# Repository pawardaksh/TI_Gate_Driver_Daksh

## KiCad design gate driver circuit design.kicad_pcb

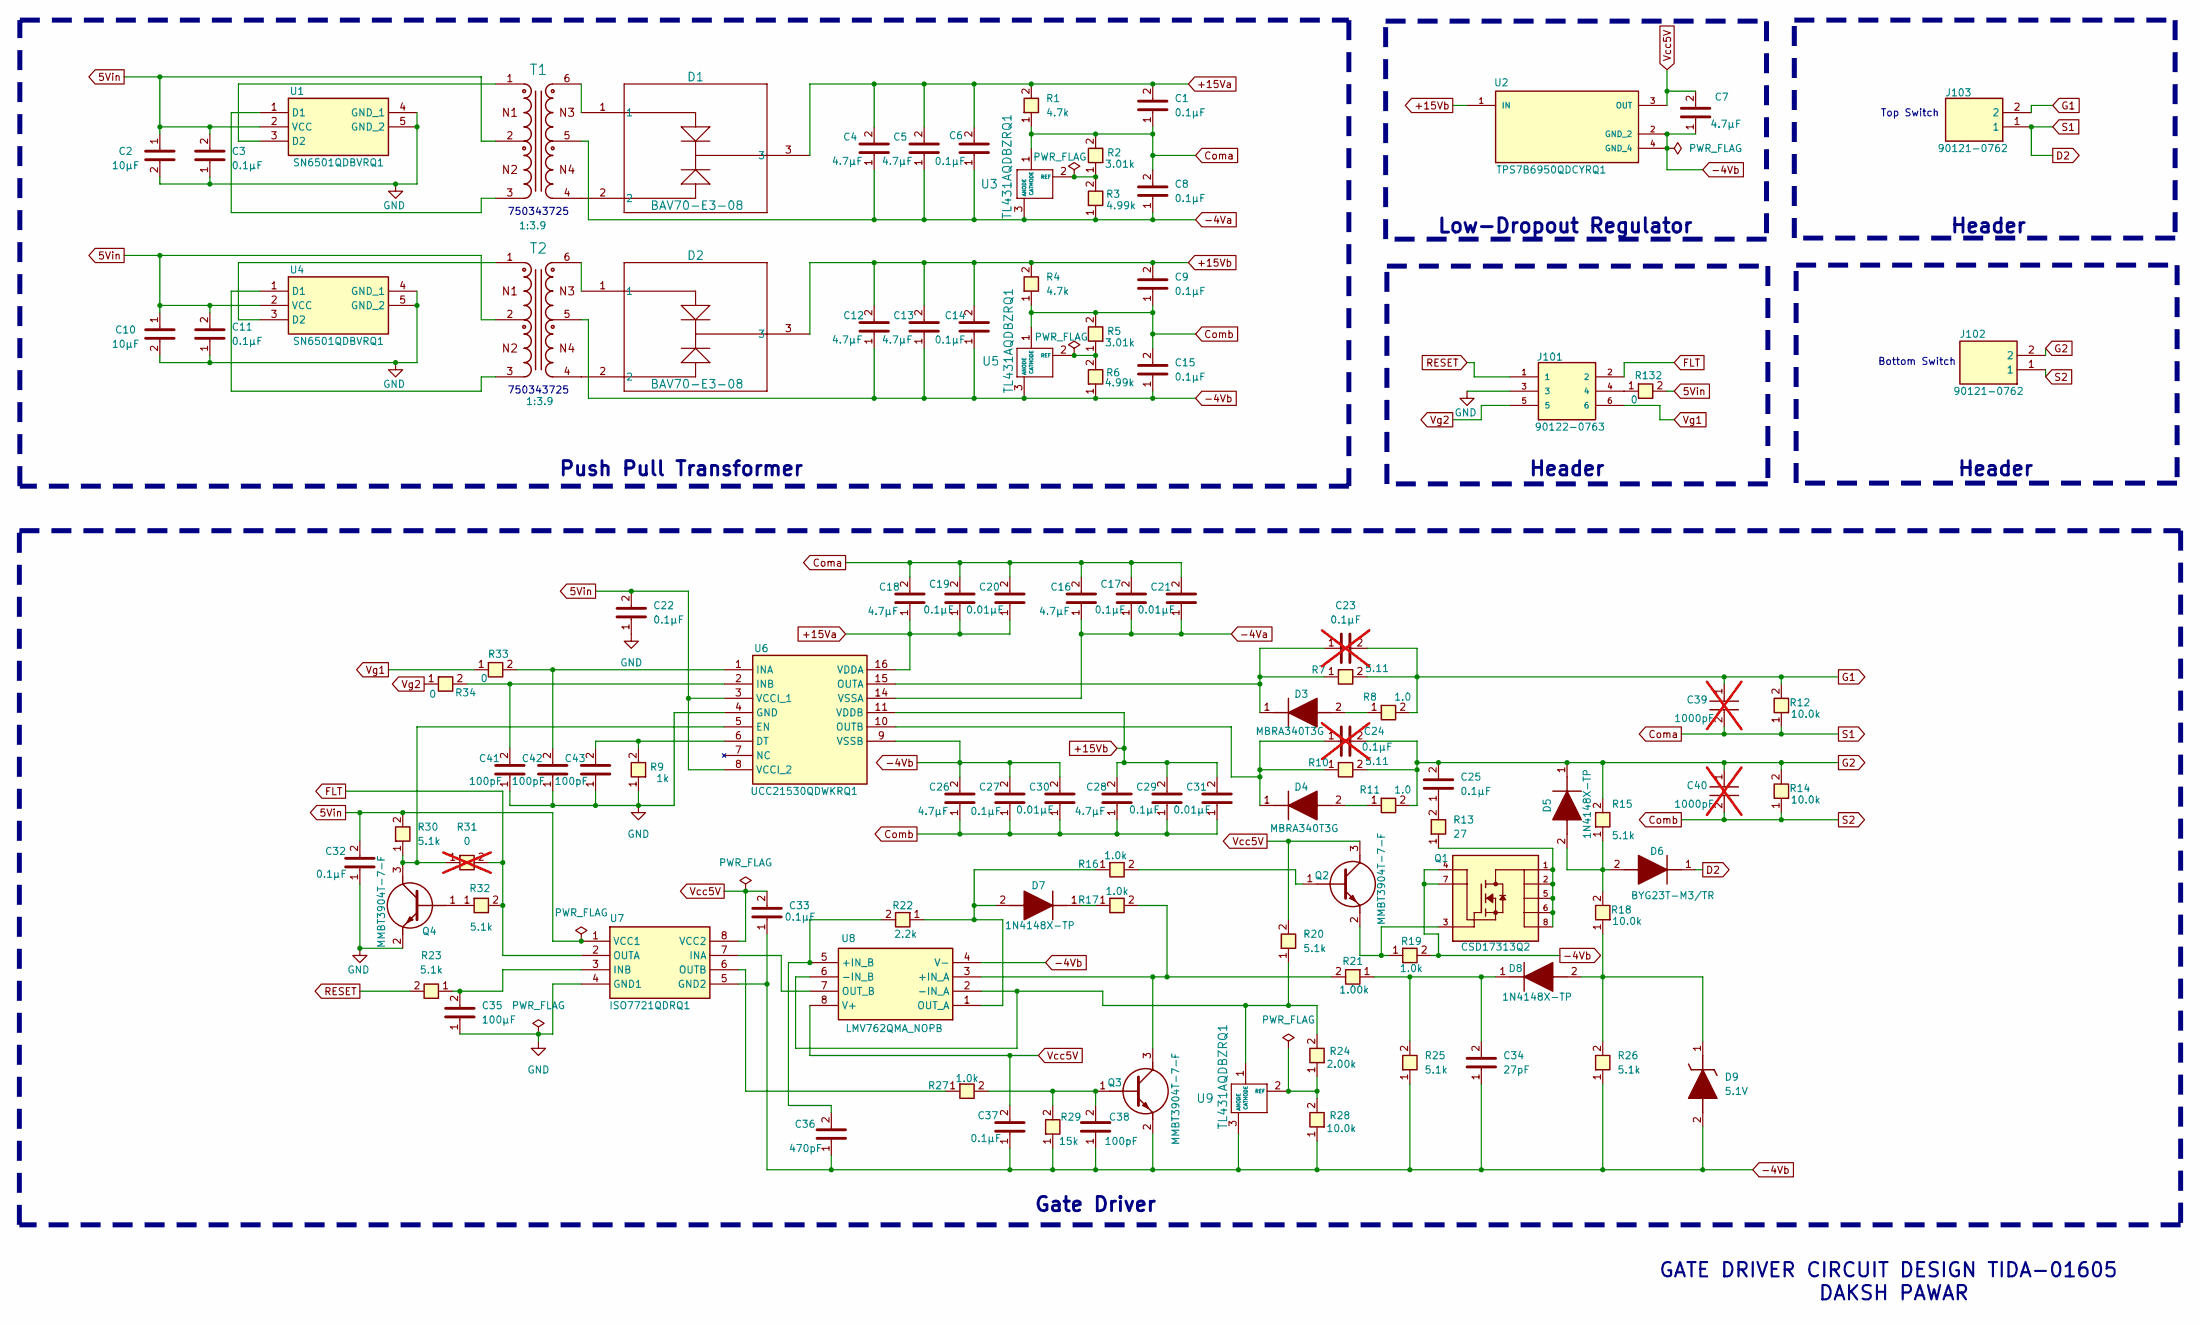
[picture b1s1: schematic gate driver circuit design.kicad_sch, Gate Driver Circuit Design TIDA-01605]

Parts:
C1, C3, C6, C8, C9, C11, C14, C15, C17, C19, C22, C25, C27, C29, C32, C33, C37: 0.1µF; CAPC2012X90N; Mouser Part Number 791-0805B104K250CT
C2, C10: 10µF; CAPC2012X135N; Mouser Part Number 963-LMK212ABJ106KGHT
C4, C5, C7, C12, C13, C16, C18, C26, C28: 4.7µF; GRT21BR61E226ME13L; Mouser Part Number 81-GRT21BR61H475KE3L
C20, C21, C30, C31: 0.01µF; CAPC2012X95N; Mouser Part Number 81-GRM215C1H103JA01D
C23, C24: 0.1µF; CAPC2012X95N; Mouser Part Number 603-AC805KRX7R8BB104; not fitted
C34: 27pF; CAPC2012X70N; Mouser Part Number 603-CC805JRNPO9BN270
C35: 100µF; CAPC2012X75N; Mouser Part Number 187-CL21C101JBANNNC
C36: 470pF; C0805; Mouser Part Number 80-C0805C471J5G
C38, C41, C42, C43: 100pF; C0805; Mouser Part Number 80-C0805C101J1GAUTO
C39, C40: 1000pF; C0805; Manufacturer_Part_Number C0805C102K5RACAUTO; not fitted
D1, D2: BAV70-E3-08; SOT_70-E3-08_VIS
D3, D4: MBRA340T3G; DIOM5226X220N; Manufacturer_Part_Number MBRA340T3G; Mouser Part Number 863-MBRA340T3G
D5, D7, D8: 1N4148X-TP; SODFL1608X70N; Manufacturer_Part_Number 1N4148X-TP; Mouser Part Number 833-1N4148X-TP
D6: BYG23T-M3/TR; DIOM5127X229N; Manufacturer_Part_Number BYG23T-M3/TR; Mouser Part Number 78-BYG23T-M3/TR
D9: 5.1V; SOD3716X135N; Mouser Part Number 78-BZT52C5V1-G3-08
J101: 90122-0763; MOLEX_90122-0763; PARTREV M3
J102, J103: 90121-0762; HDRRA2W64P0X254_1X2_508X250X360P; Mouser Part Number 538-90121-0762
Q1: CSD17313Q2; TRANS_CSD17313Q2; PARTREV E
Q2, Q3, Q4: MMBT3904T-7-F; SOT50P160X90-3N; Manufacturer_Part_Number MMBT3904T-7-F; Mouser Part Number 621-MMBT3904T-F
R1, R4: 4.7k; RESC2012X50N; Mouser Part Number 71-CRCW0805J-4.7K-E3
R2, R5: 3.01k; RESC2012X60N; Mouser Part Number 603-RT0805DRE073K01L
R3, R6: 4.99k; RESC2013X65N; Mouser Part Number 754-RR1220P-4991D-M
R7, R10: 5.11; RESC3216X60N; Mouser Part Number 71-CRCW12065R11FKEA
R8, R11: 1.0; RESC3116X65N; Mouser Part Number 652-CRM1206JW1R0ELF
R9: 1k; RESC2012X60N; Mouser Part Number 652-CR0805-F/1R00ELF
R12, R14: 10.0k; RESC2012X60N; Mouser Part Number 71-CRCW080510K0FKEBC
R13: 27; RESC3216X60N; Mouser Part Number 71-CRCW1206J-27-E3
R15, R20, R23, R25, R26, R30, R32: 5.1k; RESC2012X60N; Mouser Part Number 652-CR0805FX-5101ELF
R16, R17, R19, R27: 1.0k; RESC2012X60N; Mouser Part Number 603-RC0805JR-131KL
R18: 10.0k; RESC2012X60N; Mouser Part Number 667-ERA-6AEB103V
R21: 1.00k; RESC2012X60N; Mouser Part Number 791-RMC1/16K102FTP
R22: 2.2k; RESC2012X60N; Mouser Part Number 652-CR0805JW-222ELF
R24: 2.00k; RESC2012X60N; Mouser Part Number 708-RNCP0805FTD2K00
R28: 10.0k; RESC2012X60N; Mouser Part Number 708-RNCF0805DTE10K0
R29: 15k; RESC2012X50N; Mouser Part Number 71-CRCW0805J-15K-E3
R31: 0; ERJS06_U06__0805_; Mouser Part Number 667-ERJ-U060R00V; not fitted
R33: 0; RESC2012X60N; Mouser Part Number 667-ERJ-U060R00V
R34, R132: 0; ERJS06_U06__0805_; Mouser Part Number 667-ERJ-U060R00V
T1, T2: 750343725; TRANSFORMER_750343725_WRE-L; Input Voltage 5VDC; Output Voltage 1 19.5V; Manufacturer Part Number 750343725
U1, U4: SN6501QDBVRQ1; SOT95P280X145-5N; Mouser Part Number 595-SN6501QDBVRQ1
U2: TPS7B6950QDCYRQ1; VREG_TPS7B6950QDCYRQ1; PARTREV B
U3, U5, U9: TL431AQDBZRQ1; DBZ3
U6: UCC21530QDWKRQ1; Manufacturer_Part_Number UCC21530QDWKRQ1; Mouser Part Number 595-UCC21530QDWKRQ1
U7: ISO7721QDRQ1; SOIC127P600X175-8N; Manufacturer_Part_Number ISO7721QDRQ1; Mouser Part Number 595-ISO7721QDRQ1
U8: LMV762QMA_NOPB; SOIC127P600X175-8N; Manufacturer_Part_Number LMV762QMA/NOPB; Mouser Part Number 595-LMV762QMA/NOPB

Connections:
5Vin: C2.1, C3.2, C10.1, C11.2, C22.2, C32.2, R30.2, R132.2, T1.2, T2.2, U1.2 (VCC), U4.2 (VCC), U6.3 (VCCI_1), U6.8 (VCCI_2), U7.1 (VCC1)
+15Va: C1.2, C4.2, C5.2, C6.2, C18.1, C19.1, C20.1, D1.3, R1.2, U6.16 (VDDA)
+15Vb: C9.2, C12.2, C13.2, C14.2, C28.2, C29.2, C31.2, D2.3, R4.2, U2.1 (IN), U6.11 (VDDB)
-4Va: C4.1, C5.1, C6.1, C8.1, C16.1, C17.1, C21.1, R3.1 (R1), T1.5, U3.3 (ANODE), U6.14 (VSSA)
-4Vb: C7.1, C12.1, C13.1, C14.1, C15.1, C26.2, C27.2, C30.2, C33.1, C34.1, C36.1, C37.1, C38.1, D9.2 (A), Q1.4, Q1.7, Q3.2 (E), R6.1 (R1), R19.2, R25.1, R26.1, R28.1, R29.1, T2.5, U2.2 (GND_2), U2.4 (GND_4), U5.3 (ANODE), U6.9 (VSSB), U7.5 (GND2), U8.4 (V-), U9.3 (ANODE)
Coma: C1.1, C8.2, C16.2, C17.2, C18.2, C19.2, C20.2, C21.2, C39.2, D6.1 (K), J103.1, R1.1, R2.2, R12.1, U3.1 (CATHODE)
Comb: C9.1, C15.2, C26.1, C27.1, C28.1, C29.1, C30.1, C31.1, C40.2, J102.1, R4.1, R5.2, R14.1, U5.1 (CATHODE)
FLT: J101.2, R31.2, R32.2, U7.2 (OUTA)
G1: C23.2, C39.1, J103.2, R7.2, R8.2, R12.2
G2: C24.2, C25.2, C40.1, D5.1 (K), J102.2, R10.2, R11.2, R14.2, R15.2
GND: C2.2, C3.1, C10.2, C11.1, C22.1, C32.1, C35.1, C41.1, C42.1, C43.1, J101.3, Q4.2 (E), R9.1, U1.4 (GND_1), U1.5 (GND_2), U4.4 (GND_1), U4.5 (GND_2), U6.4 (GND), U7.4 (GND1)
unnamed: C25.1, R13.2
unnamed: D1.1, T1.6
unnamed: D1.2, T1.4
unnamed: D2.1, T2.6
unnamed: D2.2, T2.4
unnamed: D3.2 (A), R8.1
unnamed: C23.1, D3.1 (K), R7.1, U6.15 (OUTA)
unnamed: D4.2 (A), R11.1
unnamed: C24.1, D4.1 (K), R10.1, U6.10 (OUTB)
unnamed: D5.2 (A), D6.2 (A), R15.1, R18.2
unnamed: D7.2 (A), R16.1, R22.1, U8.1 (OUT_A)
unnamed: D7.1 (K), R17.1
unnamed: D8.2 (A), D9.1 (K), R18.1, R26.2
unnamed: C34.2, D8.1 (K), R21.1, R25.2
unnamed: J101.4, R132.1
unnamed: Q1.1, Q1.2, Q1.5, Q1.6, Q1.8, R13.1
unnamed: Q2.1 (B), R16.2
unnamed: Q1.3, Q2.2 (E), R19.1
unnamed: C38.2, Q3.1 (B), R27.2, R29.2
unnamed: Q3.3 (C), R17.2, R21.2, U8.3 (+IN_A)
unnamed: Q4.1 (B), R32.1
unnamed: Q4.3 (C), R30.1, R31.1, U6.5 (EN)
unnamed: R2.1, R3.2 (R2), U3.2 (REF)
unnamed: R5.1, R6.2 (R2), U5.2 (REF)
unnamed: T1.3, U1.1 (D1)
unnamed: T1.1, U1.3 (D2)
unnamed: T2.3, U4.1 (D1)
unnamed: T2.1, U4.3 (D2)
unnamed: C43.2, R9.2, U6.6 (DT)
unnamed: C42.2, R33.2, U6.1 (INA)
unnamed: C41.2, R34.2, U6.2 (INB)
unnamed: U7.7 (INA), U8.7 (OUT_B)
unnamed: C35.2, R23.1, U7.3 (INB)
unnamed: R27.1, U7.6 (OUTB)
unnamed: C36.2, R22.2, U8.5 (+IN_B)
unnamed: R20.1, R24.2, U8.2 (-IN_A), U8.6 (-IN_B), U9.1 (CATHODE)
unnamed: R24.1, R28.2, U9.2 (REF)
RESET: J101.1, R23.2
Vcc5V: C7.2, C33.2, C37.2, Q2.3 (C), R20.2, U2.3 (OUT), U7.8 (VCC2), U8.8 (V+)
Vg1: J101.6, R33.1
Vg2: J101.5, R34.1

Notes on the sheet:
GATE DRIVER CIRCUIT DESIGN TIDA-01605 DAKSH PAWAR
750343725
Bottom Switch
Header
Gate Driver
Top Switch
Push Pull Transformer
Low-Dropout Regulator

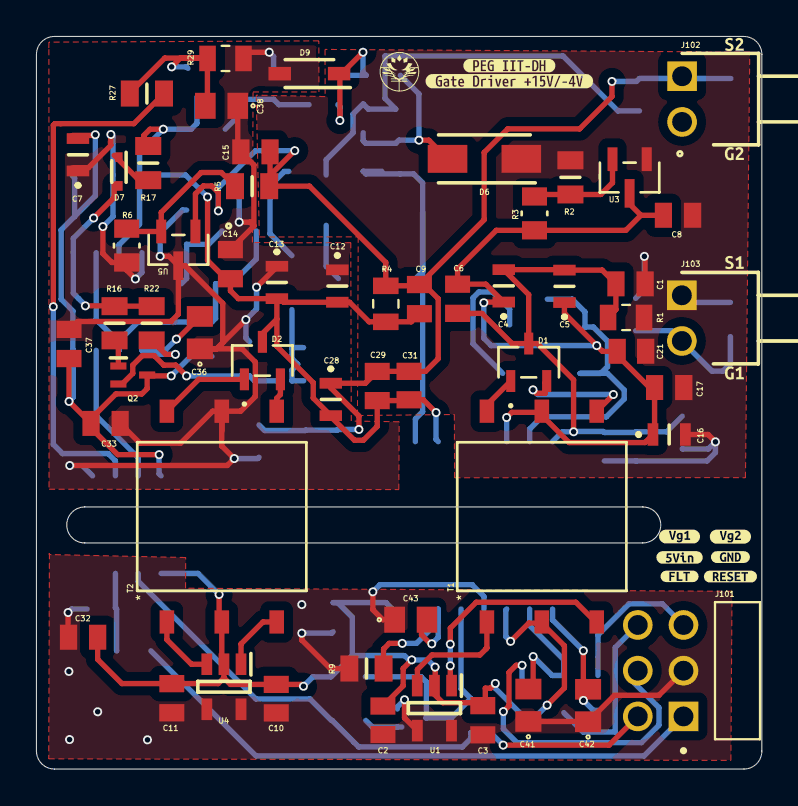
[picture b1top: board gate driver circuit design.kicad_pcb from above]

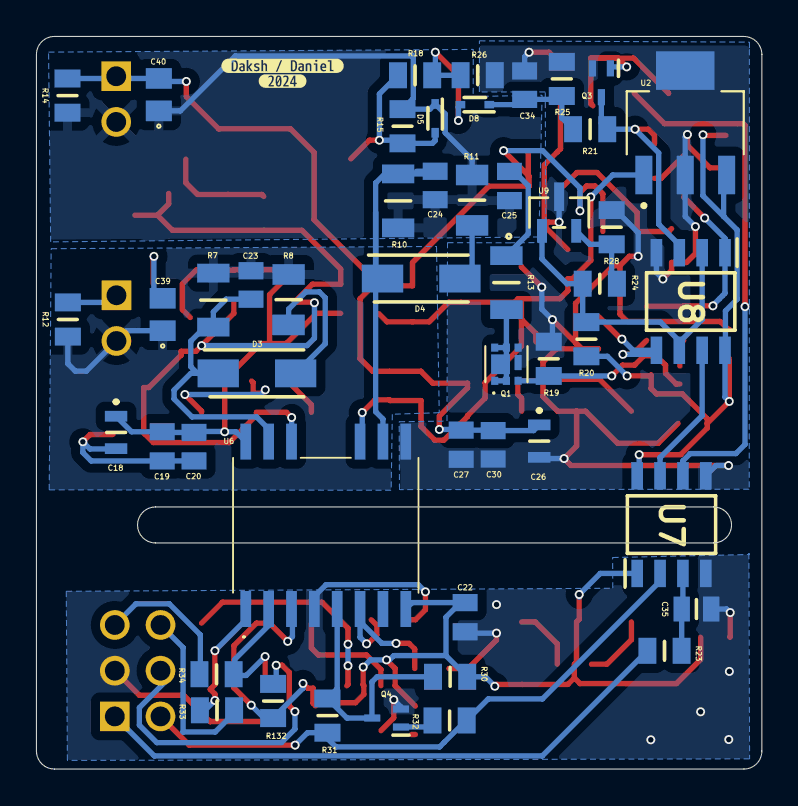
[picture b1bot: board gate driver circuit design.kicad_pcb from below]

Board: 2 copper layers, 40.3 x 40.7 mm, 119 parts (51 on the bottom side), 52 nets.

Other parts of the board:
kibuzzard-666C5A2D: G***; kibuzzard-666C5A2D
kibuzzard-666C5A3A: G***; kibuzzard-666C5A3A
kibuzzard-666C5A3F: G***; kibuzzard-666C5A3F
kibuzzard-666C5A33: G***; kibuzzard-666C5A33
kibuzzard-666C5A43: G***; kibuzzard-666C5A43
kibuzzard-666C5A49: G***; kibuzzard-666C5A49
kibuzzard-666C5B08: G***; kibuzzard-666C5B08
kibuzzard-666C5B11: G***; kibuzzard-666C5B11
kibuzzard-666C5DC5: G***; kibuzzard-666C5DC5
kibuzzard-666C5DEE: G***; kibuzzard-666C5DEE
kibuzzard-666C5E10: G***; kibuzzard-666C5E10
kibuzzard-666C5967: G***; kibuzzard-666C5967
kibuzzard-666C5988: G***; kibuzzard-666C5988
kibuzzard-666C5994: G***; kibuzzard-666C5994

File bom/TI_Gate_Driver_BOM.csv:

"Id";"Designator";"Footprint";"Quantity";"Designation";"Supplier and ref";
1;"C16,C7,C13,C5,C4,C28,C12,C26,C18";"GRT21BR61E226ME13L";9;"4.7µF";;;
2;"D9";"SOD3716X135N";1;"5.1V";;;
3;"C11,C1,C9,C15,C32,C8,C29,C17,C6,C37,C14,C33,C3,C25,C19,C22,C27";"CAPC2012X90N";17;"0.1µF";;;
4;"C42,C41,C38,C43";"C0805";4;"100pF";;;
5;"C21,C31,C20,C30";"CAPC2012X95N";4;"0.01µF";;;
6;"R22";"RESC2012X60N";1;"2.2k";;;
7;"J103,J102";"HDRRA2W64P0X254_1X2_508X250X360P";2;"90121-0762";;;
8;"R17,R16,R27,R19";"RESC2012X60N";4;"1.0k";;;
9;"T1,T2";"TRANSFORMER_750343725_WRE-L";2;"750343725";;;
10;"C2,C10";"CAPC2012X135N";2;"10µF";;;
11;"U1,U4";"SOT95P280X145-5N";2;"SN6501QDBVRQ1";;;
12;"D7,D8,D5";"SODFL1608X70N";3;"1N4148X-TP";;;
13;"J101";"MOLEX_90122-0763";1;"90122-0763";;;
14;"R6,R3";"RESC2013X65N";2;"4.99k";;;
15;"R29";"RESC2012X50N";1;"15k";;;
16;"R2,R5";"RESC2012X60N";2;"3.01k";;;
17;"D2,D1";"SOT_70-E3-08_VIS";2;"BAV70-E3-08";;;
18;"R4,R1";"RESC2012X50N";2;"4.7k";;;
19;"Q2,Q4,Q3";"SOT50P160X90-3N";3;"MMBT3904T-7-F";;;
20;"C36";"C0805";1;"470pF";;;
21;"R9";"RESC2012X60N";1;"1k";;;
22;"U5,U3,U9";"DBZ3";3;"TL431AQDBZRQ1";;;
23;"D6";"DIOM5127X229N";1;"BYG23T-M3/TR";;;
24;"R33,R132,R34,R31";"RESC2012X60N";4;"0";;;
25;"C40,C39";"C0805";2;"1000pF";;;
26;"R13";"RESC3216X60N";1;"27";;;
27;"U2";"VREG_TPS7B6950QDCYRQ1";1;"TPS7B6950QDCYRQ1";;;
28;"R24";"RESC2012X60N";1;"2.00k";;;
29;"R30,R20,R26,R23,R15,R32,R25";"RESC2012X60N";7;"5.1k";;;
30;"R11,R8";"RESC3116X65N";2;"1.0";;;
31;"U7";"SOIC127P600X175-8N";1;"ISO7721QDRQ1";;;
32;"R14,R28,R12,R18";"RESC2012X60N";4;"10.0k";;;
33;"R7,R10";"RESC3216X60N";2;"5.11";;;
34;"C23,C24";"CAPC2012X95N";2;"0.1µF";;;
35;"C34";"CAPC2012X70N";1;"27pF";;;
36;"D3,D4";"DIOM5226X220N";2;"MBRA340T3G";;;
37;"R21";"RESC2012X60N";1;"1.00k";;;
38;"U8";"SOIC127P600X175-8N";1;"LMV762QMA_NOPB";;;
39;"C35";"CAPC2012X75N";1;"100µF";;;
40;"U6";"UCC21530QDWKRQ1";1;"UCC21530QDWKRQ1";;;
41;"Q1";"TRANS_CSD17313Q2";1;"CSD17313Q2";;;

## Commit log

2024-05-24 Initial schematic drawn for TI gate driver
    TI TIDA 01605 gate driver reference design schematic started in KiCad.
2024-05-27 Completed schematic design of gate driver
    added components to schematic 27th May 2024
2024-05-31 Schematic Design Completed For Gate Driver
    Schematic Design Completed For Gate Driver
2024-06-05 SCHEMATIC FINAL
    FINAL DESIGN OF SCHEMATIC
2024-06-07 PLACED COMPONENTS ON PCB AND DESIGNED 3D MODEL OF PCB
    PLACED COMPONENTS ON PCB AND DESIGNED 3D MODEL OF PCB
2024-06-11 Almost Done Routing Of PCB
    Some Connections are remaining , Almost Done Routing Of PCB
2024-06-12 routing
    routing
2024-06-13 PCB Routing Last Stage
    PCB Routing Last Stage
2024-06-14 Final PCB design TI gate driver
    TI gate driver final PCB design files
2024-06-29 added invoice PCB power
2024-07-02 Added board images
